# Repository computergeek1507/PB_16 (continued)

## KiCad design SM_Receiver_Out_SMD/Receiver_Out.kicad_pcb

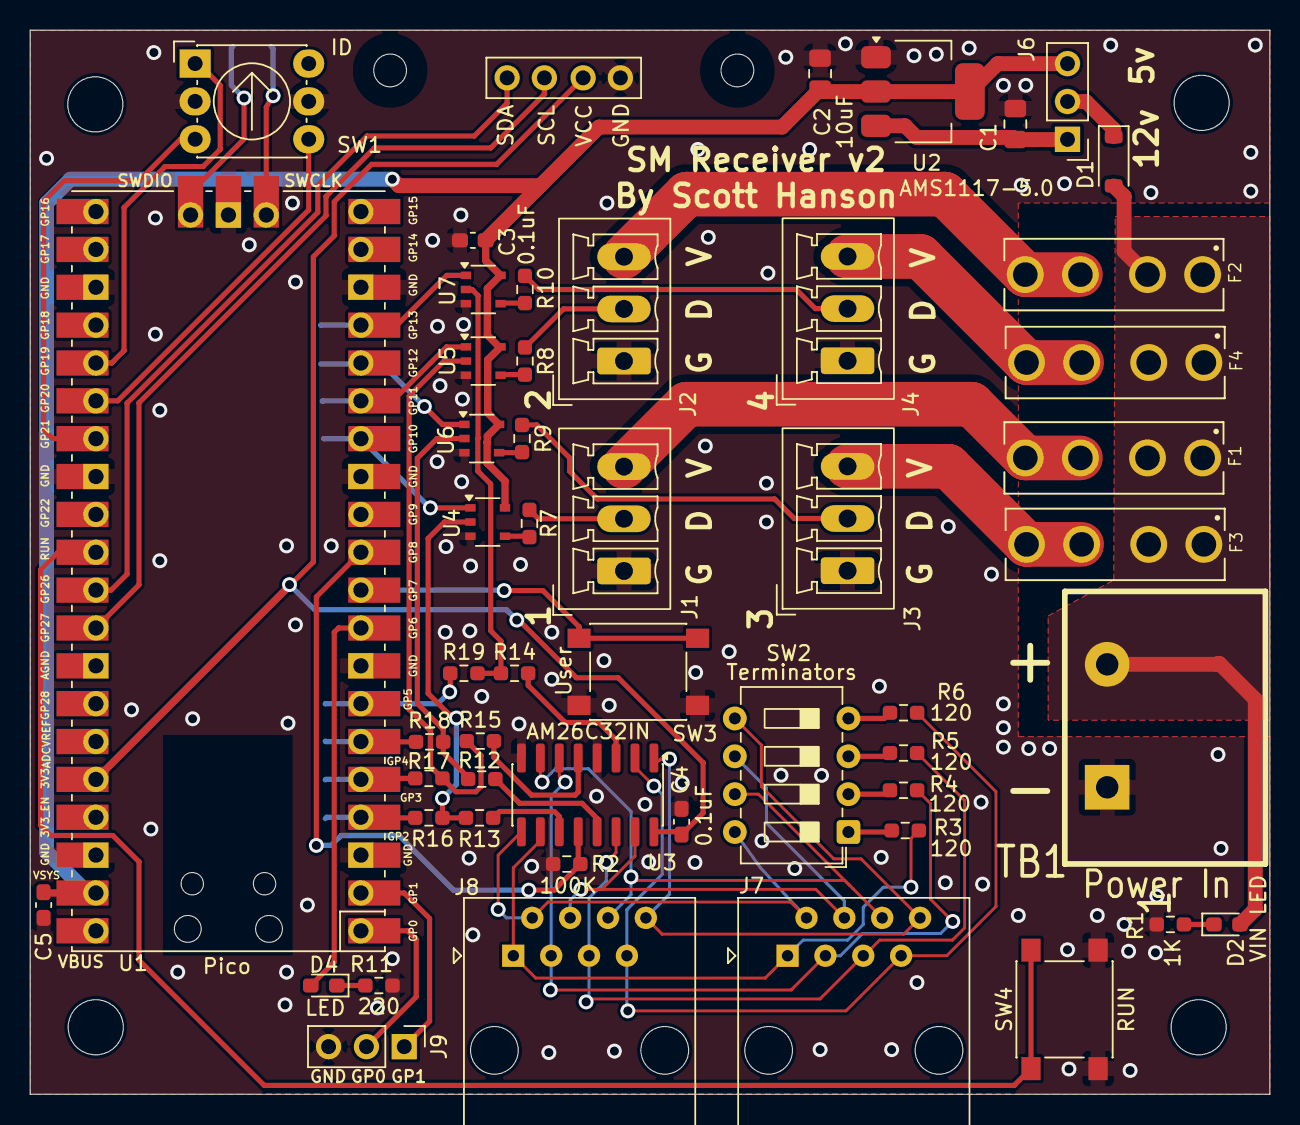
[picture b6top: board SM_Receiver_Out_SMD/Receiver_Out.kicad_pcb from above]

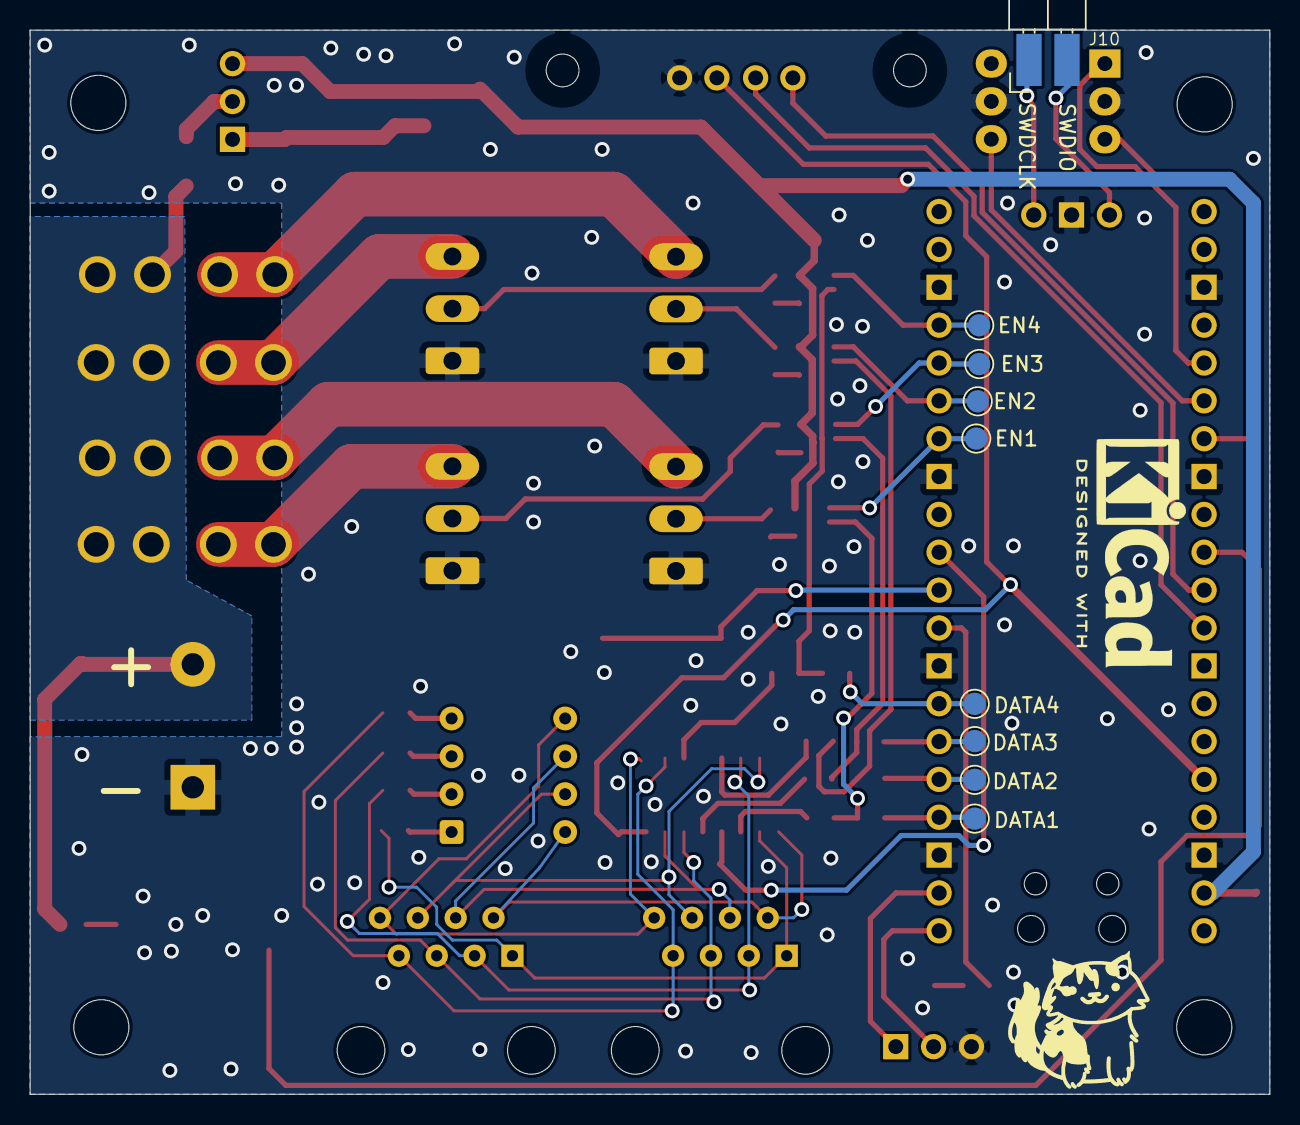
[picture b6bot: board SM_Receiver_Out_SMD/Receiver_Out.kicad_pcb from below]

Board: 2 copper layers, 83.2 x 71.4 mm, 65 parts (9 on the bottom side), 61 nets.

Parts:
C1, C2: 10uF; C_0805_2012Metric_Pad1.18x1.45mm_HandSolder
C3, C4, C5: 0.1uF; C_0603_1608Metric_Pad1.08x0.95mm_HandSolder
D1: B5819W; D_SOD-123
D2: VIN LED; LED_0603_1608Metric_Pad1.05x0.95mm_HandSolder
D4: LED; LED_0603_1608Metric_Pad1.05x0.95mm_HandSolder
F1, F2, F3, F4: 3544-2; FUSE_3544-2
H1, H2, H3, H4: MountingHole; MountingHole_3.7mm
J1: String1; PhoenixContact_MCV_1,5_3-G-3.5_1x03_P3.50mm_Vertical
J2: String2; PhoenixContact_MCV_1,5_3-G-3.5_1x03_P3.50mm_Vertical
J3: String3; PhoenixContact_MCV_1,5_3-G-3.5_1x03_P3.50mm_Vertical
J4: String4; PhoenixContact_MCV_1,5_3-G-3.5_1x03_P3.50mm_Vertical
J5: OLED; OLED-SSD1306-128X64-I2C-THT
J6: VIN_Voltage; PinHeader_1x03_P2.54mm_Vertical
J7, J8: RJ45; RJ45_Amphenol_54602-x08_Horizontal
J9: Debug; PinHeader_1x03_P2.54mm_Vertical
J10: SWD; 1x02_Horizontal_SMD
R1: 1K; R_0603_1608Metric_Pad0.98x0.95mm_HandSolder
R2: 100K; R_0603_1608Metric_Pad0.98x0.95mm_HandSolder
R3, R4, R5, R6: 120; R_0603_1608Metric_Pad0.98x0.95mm_HandSolder
R7, R8, R9, R10: 33ohm; R_0603_1608Metric_Pad0.98x0.95mm_HandSolder
R11: 220; R_0603_1608Metric_Pad0.98x0.95mm_HandSolder
R12, R13, R14, R15, R16, R17, R18, R19: 100ohm; R_0603_1608Metric_Pad0.98x0.95mm_HandSolder
SW1: ID; Nidec_Copal_SH-7010C
SW2: Terminators; SW_DIP_SPSTx04_Slide_6.7x11.72mm_W7.62mm_P2.54mm_LowProfile
SW3: User; SW_Push_1P1T_NO_6x6mm_H9.5mm
SW4: RUN; SW_Push_1P1T_NO_6x6mm_H9.5mm
TB1: Power In; BARRIER_BLOCK_1ROW_2POS
TP1: DATA1; TestPoint_Pad_D1.5mm
TP2: DATA2; TestPoint_Pad_D1.5mm
TP3: DATA3; TestPoint_Pad_D1.5mm
TP4: DATA4; TestPoint_Pad_D1.5mm
TP5: EN1; TestPoint_Pad_D1.5mm
TP6: EN2; TestPoint_Pad_D1.5mm
TP7: EN3; TestPoint_Pad_D1.5mm
TP8: EN4; TestPoint_Pad_D1.5mm
U1: Pico; RPi_Pico_SMD_TH
U2: AMS1117-5.0; SOT-223-3_TabPin2
U3: AM26C32IN; SOIC-16_3.9x9.9mm_P1.27mm
U4, U5, U6, U7: 74AHCT1G125; TSOP-5_1.65x3.05mm_P0.95mm

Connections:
+3V3: C4.1, J5.3, U1.36 (3V3), U3.16 (VCC)
+5V: C2.1, C3.1, C5.1, J6.3, U1.39 (VSYS), U2.2 (VO), U4.5 (VCC), U5.5 (VCC), U6.5 (VCC), U7.5 (VCC)
/Micro/SCL: J5.2, U1.32 (GPIO27_ADC1)
/Micro/SDA: J5.1, U1.31 (GPIO26_ADC0)
/Micro/SWDCLK: J10.1, U1.41 (SWCLK)
/Micro/SWDIO: J10.2, U1.43 (SWDIO)
/Outputs/DOUT1: J1.2, R7.1
/Outputs/DOUT2: J2.2, R8.1
/Outputs/DOUT3: J3.2, R9.1
/Outputs/DOUT4: J4.2, R10.1
/Outputs/VOUT1: F1.2_1 (2), F1.2_2 (2), J1.3
/Outputs/VOUT2: F2.2_1 (2), F2.2_2 (2), J2.3
/Outputs/VOUT3: F3.2_1 (2), F3.2_2 (2), J3.3
/Outputs/VOUT4: F4.2_1 (2), F4.2_2 (2), J4.3
/PWR: C1.1, J6.1, U2.3 (VI)
/VIN: D1.1 (K), J6.2
DIFF_EN: R2.1, U1.11 (GPIO8), U3.12 (EN_2)
EN1: TP5.1, U1.14 (GPIO10), U4.1
EN2: TP6.1, U1.15 (GPIO11), U5.1
EN3: TP7.1, U1.16 (GPIO12), U6.1
EN4: TP8.1, U1.17 (GPIO13), U7.1
GND: C1.2, C2.2, C3.2, C4.2, C5.2, J1.1, J2.1, J3.1, J4.1, J5.4, J9.3, R1.1, R2.2, R11.2, SW1.C, SW3.1, SW4.2, TB1.1, U1.3 (GND), U1.8 (GND), U1.13 (GND), U1.18 (GND), U1.23 (GND), U1.28 (GND), U1.38 (GND), U1.42 (GND), U2.1 (GND), U3.4 (EN), U3.8 (GND), U4.3 (GND), U5.3 (GND), U6.3 (GND), U7.3 (GND)
unnamed: D2.1 (K), R1.2
unnamed: D4.1 (K), R11.1
unnamed: D4.2 (A), U1.9 (GPIO6)
unnamed: J9.1, U1.2 (GPIO1)
unnamed: J9.2, U1.1 (GPIO0)
unnamed: R3.1, SW2.1
unnamed: R4.1, SW2.2
unnamed: R5.1, SW2.3
unnamed: R6.1, SW2.4
unnamed: R7.2, U4.4
unnamed: R8.2, U5.4
unnamed: R9.2, U6.4
unnamed: R10.2, U7.4
unnamed: R12.1, U3.13 (OUT_B)
unnamed: R13.1, U3.11 (OUT_D)
unnamed: R14.2, U3.3 (OUT_A)
unnamed: R15.2, U3.5 (OUT_C)
unnamed: R16.1, TP1.1, U1.4 (GPIO2)
unnamed: R17.1, TP2.1, U1.5 (GPIO3)
unnamed: R18.1, TP3.1, U1.6 (GPIO4)
unnamed: R19.1, TP4.1, U1.7 (GPIO5)
unnamed: SW1.1, U1.25 (GPIO19)
unnamed: SW1.2, U1.26 (GPIO20)
unnamed: SW1.4, U1.27 (GPIO21)
unnamed: SW3.2, U1.10 (GPIO7)
unnamed: SW4.1, U1.30 (RUN)
OUT17: R13.2, R16.2, U4.2
OUT18: R15.1, R17.2, U5.2
OUT19: R12.2, R18.2, U6.2
OUT20: R14.1, R19.2, U7.2
Serial1_N: J7.2, J8.2, SW2.8, U3.9 (INPUT_D-)
Serial1_P: J7.1, J8.1, R3.2, U3.10 (INPUT_D+)
Serial2_N: J7.6, J8.6, SW2.7, U3.7 (INPUT_C-)
Serial2_P: J7.3, J8.3, R4.2, U3.6 (INPUT_C+)
Serial3_N: J7.4, J8.4, SW2.6, U3.15 (INPUT_B-)
Serial3_P: J7.5, J8.5, R5.2, U3.14 (INPUT_B+)
Serial4_N: J7.8, J8.8, SW2.5, U3.1 (INPUT_A-)
Serial4_P: J7.7, J8.7, R6.2, U3.2 (INPUT_A+)
VIN1: D1.2 (A), D2.2 (A), F1.1_1 (1), F1.1_2 (1), F2.1_1 (1), F2.1_2 (1), F3.1_1 (1), F3.1_2 (1), F4.1_1 (1), F4.1_2 (1), TB1.2

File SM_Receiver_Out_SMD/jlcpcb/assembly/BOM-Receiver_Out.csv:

Comment,Designator,Footprint,LCSC
User,"SW3,SW4",SW_Push_1P1T_NO_6x6mm_H9.5mm,C127509
0.1uF,"C3,C4,C5",C_0603_1608Metric_Pad1.08x0.95mm_HandSolder,C1525
10uF,"C1,C2",C_0805_2012Metric_Pad1.18x1.45mm_HandSolder,C15850
String1,"J1,J2,J3,J4","PhoenixContact_MCV_1,5_3-G-3.5_1x03_P3.50mm_Vertical",C192778
1K,R1,R_0603_1608Metric_Pad0.98x0.95mm_HandSolder,C21190
OLED,J5,OLED-SSD1306-128X64-I2C-THT,C225501
100ohm,"R12,R13,R14,R15,R16,R17,R18,R19",R_0603_1608Metric_Pad0.98x0.95mm_HandSolder,C22775
120,"R3,R4,R5,R6",R_0603_1608Metric_Pad0.98x0.95mm_HandSolder,C22787
VIN LED,"D2,D4",LED_0603_1608Metric_Pad1.05x0.95mm_HandSolder,C2286
220,R11,R_0603_1608Metric_Pad0.98x0.95mm_HandSolder,C22962
33ohm,"R10,R7,R8,R9",R_0603_1608Metric_Pad0.98x0.95mm_HandSolder,C23140
100K,R2,R_0603_1608Metric_Pad0.98x0.95mm_HandSolder,C25803
RJ45,"J7,J8",RJ45_Amphenol_54602-x08_Horizontal,C2938579
Power In,TB1,BARRIER_BLOCK_1ROW_2POS,C306200
ID,SW1,Nidec_Copal_SH-7010C,C457921
SWD,J10,1x02_Horizontal_SMD,C492401
VIN_Voltage,"J6,J9",PinHeader_1x03_P2.54mm_Vertical,C49257
3544-2,"F1,F2,F3,F4",FUSE_3544-2,C492610
Terminators,SW2,SW_DIP_SPSTx04_Slide_6.7x11.72mm_W7.62mm_P2.54mm_LowProfile,C509571
AM26C32IN,U3,SOIC-16_3.9x9.9mm_P1.27mm,C6180
AMS1117-5.0,U2,SOT-223-3_TabPin2,C6187
74AHCT1G125,"U4,U5,U6,U7",TSOP-5_1.65x3.05mm_P0.95mm,C7484
B5819W,D1,D_SOD-123,C8598
Pico,U1,RPi_Pico_SMD_TH,

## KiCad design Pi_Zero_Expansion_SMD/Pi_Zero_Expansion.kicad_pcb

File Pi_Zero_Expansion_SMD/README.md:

# Copyright and Disclaimer
Copyright: Scott Hanson

This documentation describes Open Hardware and is licensed under the CERN Open Hardware Licence Version 2 - Strongly Reciprocal. (CERN-OHL-S)

You may redistribute and modify this documentation under the terms of the CERN OHL-S-v2 (https://ohwr.org/cern_ohl_s_v2.txt). This documentation is distributed WITHOUT ANY EXPRESS OR IMPLIED WARRANTY, INCLUDING OF MERCHANTABILITY, SATISFACTORY QUALITY AND FITNESS FOR A PARTICULAR PURPOSE. Please see the CERN OHL v2-S for applicable conditions

**Under CERN OHL-S-v2, derivative work must be publicy released as defined in subsection 3.3**

# Pi Zero Expansion 

The Pi Zero Expansion is a surface mount(SMD) controller with a single Expansion port. A total of 16 pixel outputs. All the design files are open source and available on github.

## [Interactive BOM](https://computergeek1507.github.io/PB_16/Pi_Zero_Expansion_SMD/bom/ibom)

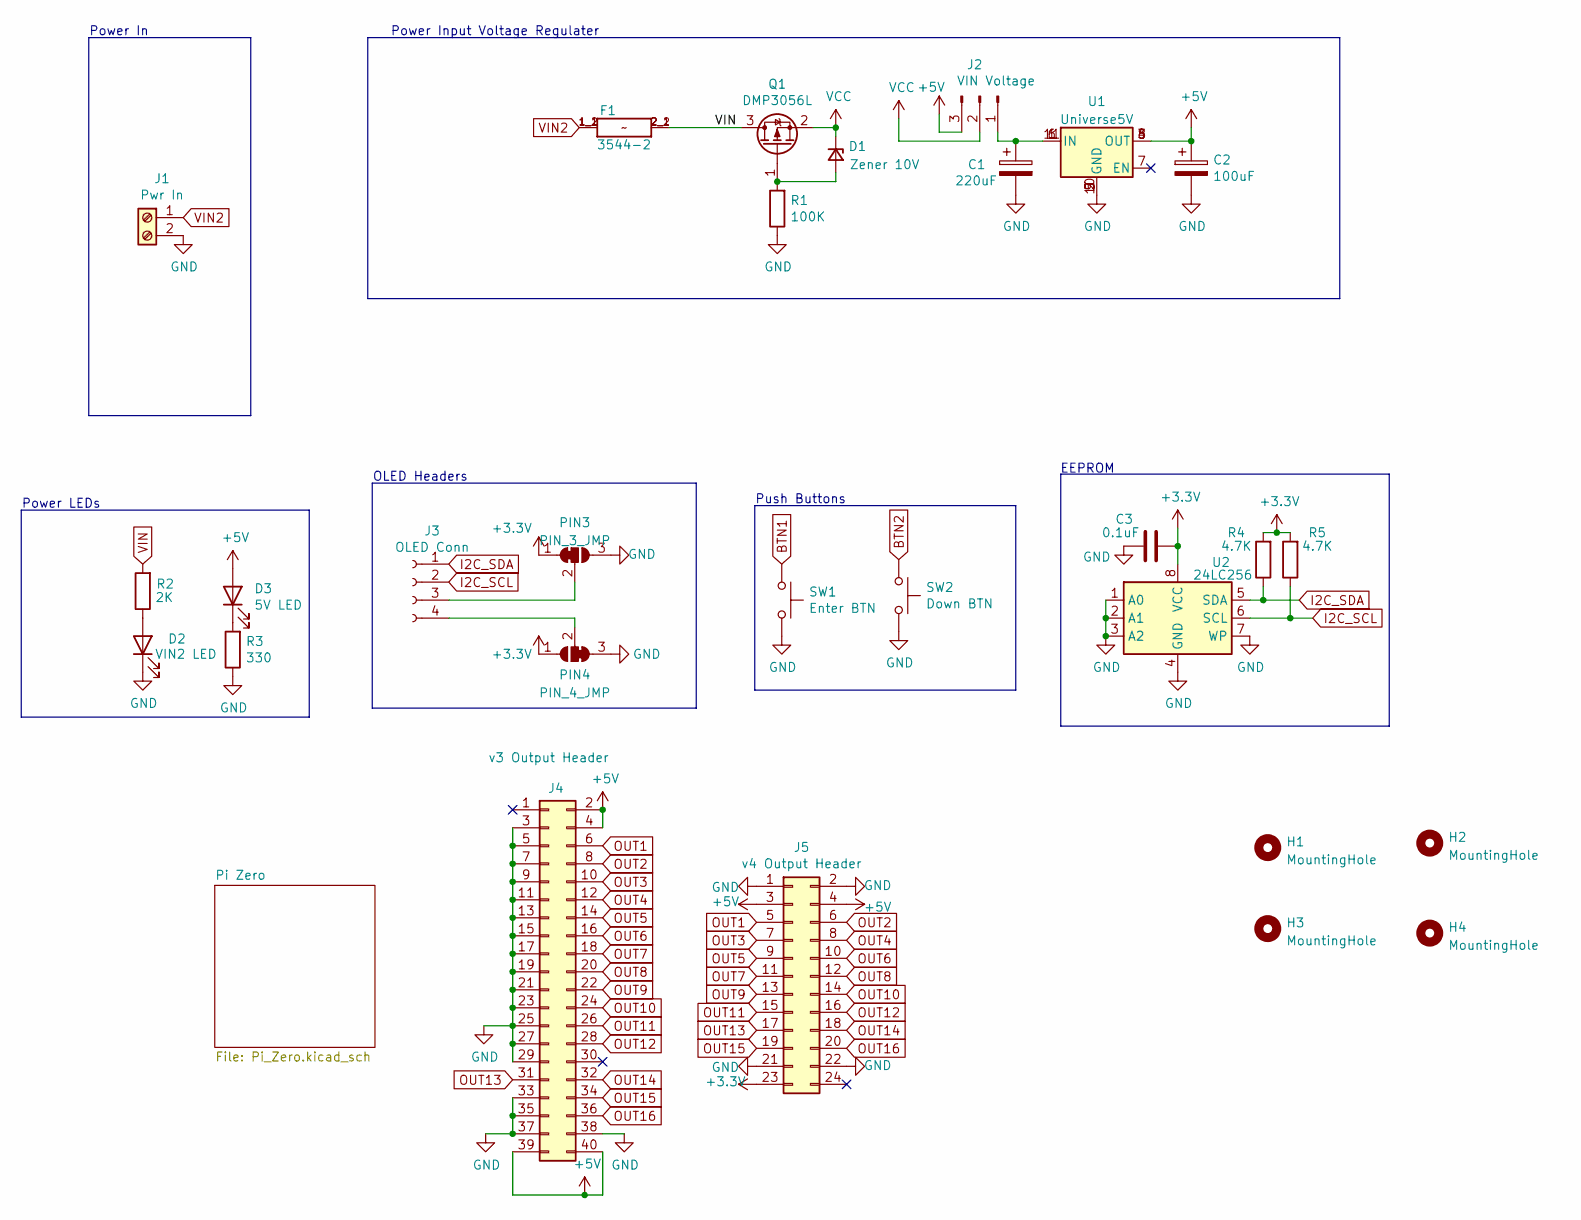
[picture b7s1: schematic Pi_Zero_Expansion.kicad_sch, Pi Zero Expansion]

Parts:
C1: 220uF; CP_Radial_D10.0mm_P5.00mm; MPN ECA-1HM221; Digi-Key_PN P5183-ND
C2: 100uF; CP_Elec_6.3x5.4_Nichicon; MPN UWX1C101MCL1GB; Digi-Key_PN 493-2105-1-ND
C3: 0.1uF; C_0603_1608Metric_Pad1.08x0.95mm_HandSolder; MPN CL10B104KB8NNWC; Digi-Key_PN 1276-1935-2-ND
D1: Zener 10V; D_SOD-123; MPN MMSZ5240B-7-F; Digi-Key_PN MMSZ5240B-FDICT-ND
D2: VIN2 LED; LED_0603_1608Metric_Pad1.05x0.95mm_HandSolder; MPN LTST-C190KRKT; Digi-Key_PN 160-1436-2-ND
D3: 5V LED; LED_0603_1608Metric_Pad1.05x0.95mm_HandSolder; MPN LTST-C190KRKT; Digi-Key_PN 160-1436-2-ND
F1: 3544-2; FUSE_3544-2; MPN 3544-2; Digi-Key_PN 36-3544-2-ND
H1, H2, H3, H4: MountingHole; MountingHole_3.7mm
J1: Pwr In; PHOENIX_MKDS1_2-3.81; MPN 1727010; Digi-Key_PN 277-1947-ND
J2: VIN Voltage; PinHeader_1x03_P2.54mm_Vertical; MPN 61300311121; Digi-Key_PN 732-5316-ND
J3: OLED Conn; PinSocket_1x04_P2.54mm_Vertical; MPN PPTC041LFBN-RC; Digi-Key_PN S7002-ND
J4: v3 Output Header; IDC-Header_2x20_P2.54mm_Vertical; MPN SBH11-PBPC-D20-ST-BK; Digi-Key_PN S9175-ND
J5: v4 Output Header; IDC-Header_2x12_P2.54mm_Vertical; MPN Z-S311024S1GK1A; Digi-Key_PN ED10525-ND
PIN3: PIN_3_JMP; SolderJumper-3_P1mm_Bridged12
PIN4: PIN_4_JMP; SolderJumper-3_P1mm_Bridged23
Q1: DMP3056L; SOT-23; MPN DMP3056L-7; Digi-Key_PN DMP3056L-7DICT-ND
R1: 100K; R_0603_1608Metric_Pad0.98x0.95mm_HandSolder; MPN RT0603BRD07100KL; Digi-Key_PN YAG1235CT-ND
R2: 2K; R_0603_1608Metric_Pad0.98x0.95mm_HandSolder; LCSC C4190
R3: 330; R_0603_1608Metric_Pad0.98x0.95mm_HandSolder; LCSC C23138
R4, R5: 4.7K; R_0603_1608Metric_Pad0.98x0.95mm_HandSolder; MPN RC0603JR-074K7L; Digi-Key_PN 311-4.7KGRCT-ND
SW1: Enter BTN; SW_Push_1P1T_NO_6x6mm_H9.5mm; MPN PTS645SL50SMTR92 LFS; Digi-Key_PN CKN9088CT-ND
SW2: Down BTN; SW_Push_1P1T_NO_6x6mm_H9.5mm; MPN PTS645SL50SMTR92 LFS; Digi-Key_PN CKN9088CT-ND
U1: Universe5V; Universal_5V_Horizontal
U2: 24LC256; SOIC-8_3.9x4.9mm_P1.27mm; MPN 24LC256T-I/SN; Digi-Key_PN 24LC256T-I/SNCT-ND

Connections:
+3V3: C3.1, J5.23, PIN3.1 (A), PIN4.1 (A), R4.2, R5.2, U2.8 (VCC); also elsewhere on the board
+5V: C2.1, D3.2 (A), J2.3, J4.2, J4.4, J4.39, J4.40, J5.3, J5.4, U1.3 (OUT), U1.4 (OUT), U1.8 (OUT); also elsewhere on the board
BTN1: SW1.1; also elsewhere on the board
BTN2: SW2.1; also elsewhere on the board
GND: C1.2, C2.2, C3.2, D2.1 (K), J1.2, J4.3, J4.5, J4.7, J4.9, J4.11, J4.13, J4.15, J4.17, J4.19, J4.21, J4.23, J4.25, J4.27, J4.29, J4.33, J4.35, J4.37, J4.38, J5.1, J5.2, J5.21, J5.22, PIN3.3 (B), PIN4.3 (B), R1.1, R3.1, SW1.2, SW2.2, U1.2 (GND), U1.5 (GND), U1.9 (GND), U1.10 (GND), U2.1 (A0), U2.2 (A1), U2.3 (A2), U2.4 (GND), U2.7 (WP); also elsewhere on the board
I2C_SCL: J3.2, R5.1, U2.6 (SCL); also elsewhere on the board
I2C_SDA: J3.1, R4.1, U2.5 (SDA); also elsewhere on the board
unnamed: C1.1, J2.1, U1.1 (IN), U1.6 (IN), U1.11 (IN)
unnamed: D1.2 (A), Q1.1 (G), R1.2
unnamed: D2.2 (A), R2.1
unnamed: D3.1 (K), R3.2
unnamed: J3.3, PIN3.2 (C)
unnamed: J3.4, PIN4.2 (C)
OUT1: J4.6, J5.5; also elsewhere on the board
OUT2: J4.8, J5.6; also elsewhere on the board
OUT3: J4.10, J5.7; also elsewhere on the board
OUT4: J4.12, J5.8; also elsewhere on the board
OUT5: J4.14, J5.9; also elsewhere on the board
OUT6: J4.16, J5.10; also elsewhere on the board
OUT7: J4.18, J5.11; also elsewhere on the board
OUT8: J4.20, J5.12; also elsewhere on the board
OUT9: J4.22, J5.13; also elsewhere on the board
OUT10: J4.24, J5.14; also elsewhere on the board
OUT11: J4.26, J5.15; also elsewhere on the board
OUT12: J4.28, J5.16; also elsewhere on the board
OUT13: J4.31, J5.17; also elsewhere on the board
OUT14: J4.32, J5.18; also elsewhere on the board
OUT15: J4.34, J5.19; also elsewhere on the board
OUT16: J4.36, J5.20; also elsewhere on the board
VCC: D1.1 (K), J2.2, Q1.2 (S)
VIN: F1.2_1 (2), F1.2_2 (2), Q1.3 (D), R2.2
VIN2: F1.1_1 (1), F1.1_2 (1), J1.1

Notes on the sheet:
Power LEDs
Power In
OLED Headers
Push Buttons
Power Input Voltage Regulater
EEPROM

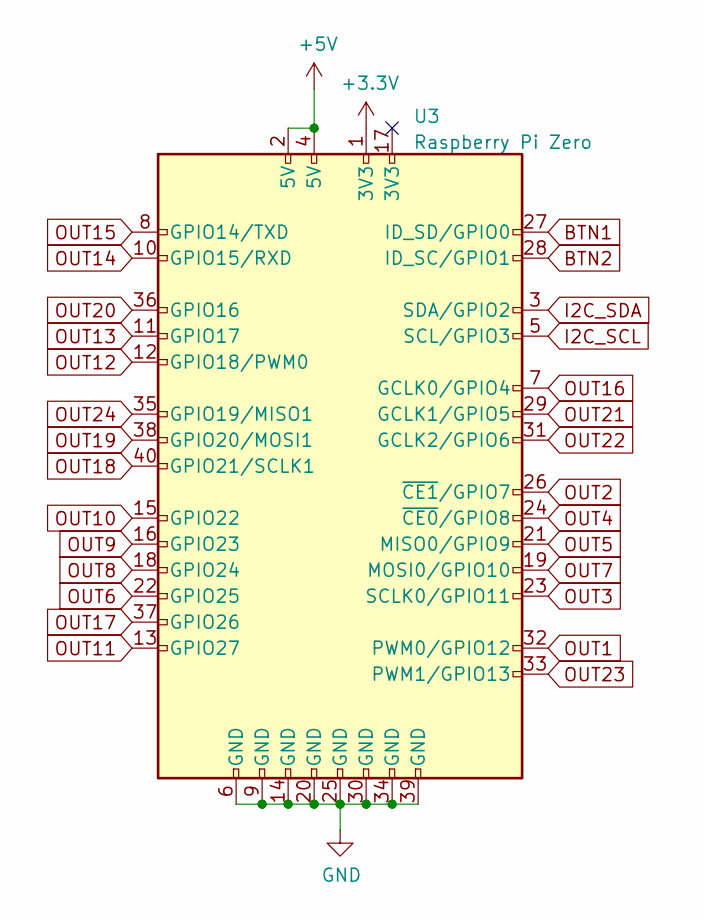
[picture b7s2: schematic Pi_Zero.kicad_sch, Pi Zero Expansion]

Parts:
U3: Raspberry Pi Zero; Raspberry_Pi_Zero_Socketed_THT_FaceDown_MountingHoles

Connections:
+3V3: U3.1 (3V3); also elsewhere on the board
+5V: U3.2 (5V), U3.4 (5V); also elsewhere on the board
BTN1: U3.27 (ID_SD/GPIO0); also elsewhere on the board
BTN2: U3.28 (ID_SC/GPIO1); also elsewhere on the board
GND: U3.6 (GND), U3.9 (GND), U3.14 (GND), U3.20 (GND), U3.25 (GND), U3.30 (GND), U3.34 (GND), U3.39 (GND); also elsewhere on the board
I2C_SCL: U3.5 (SCL/GPIO3); also elsewhere on the board
I2C_SDA: U3.3 (SDA/GPIO2); also elsewhere on the board
OUT1: U3.32 (PWM0/GPIO12); also elsewhere on the board
OUT2: U3.26 (~CE1/GPIO7); also elsewhere on the board
OUT3: U3.23 (SCLK0/GPIO11); also elsewhere on the board
OUT4: U3.24 (~CE0/GPIO8); also elsewhere on the board
OUT5: U3.21 (MISO0/GPIO9); also elsewhere on the board
OUT6: U3.22 (GPIO25); also elsewhere on the board
OUT7: U3.19 (MOSI0/GPIO10); also elsewhere on the board
OUT8: U3.18 (GPIO24); also elsewhere on the board
OUT9: U3.16 (GPIO23); also elsewhere on the board
OUT10: U3.15 (GPIO22); also elsewhere on the board
OUT11: U3.13 (GPIO27); also elsewhere on the board
OUT12: U3.12 (GPIO18/PWM0); also elsewhere on the board
OUT13: U3.11 (GPIO17); also elsewhere on the board
OUT14: U3.10 (GPIO15/RXD); also elsewhere on the board
OUT15: U3.8 (GPIO14/TXD); also elsewhere on the board
OUT16: U3.7 (GCLK0/GPIO4); also elsewhere on the board
OUT17: U3.37 (GPIO26)
OUT18: U3.40 (GPIO21/SCLK1)
OUT19: U3.38 (GPIO20/MOSI1)
OUT20: U3.36 (GPIO16)
OUT21: U3.29 (GCLK1/GPIO5)
OUT22: U3.31 (GCLK2/GPIO6)
OUT23: U3.33 (PWM1/GPIO13)
OUT24: U3.35 (GPIO19/MISO1)

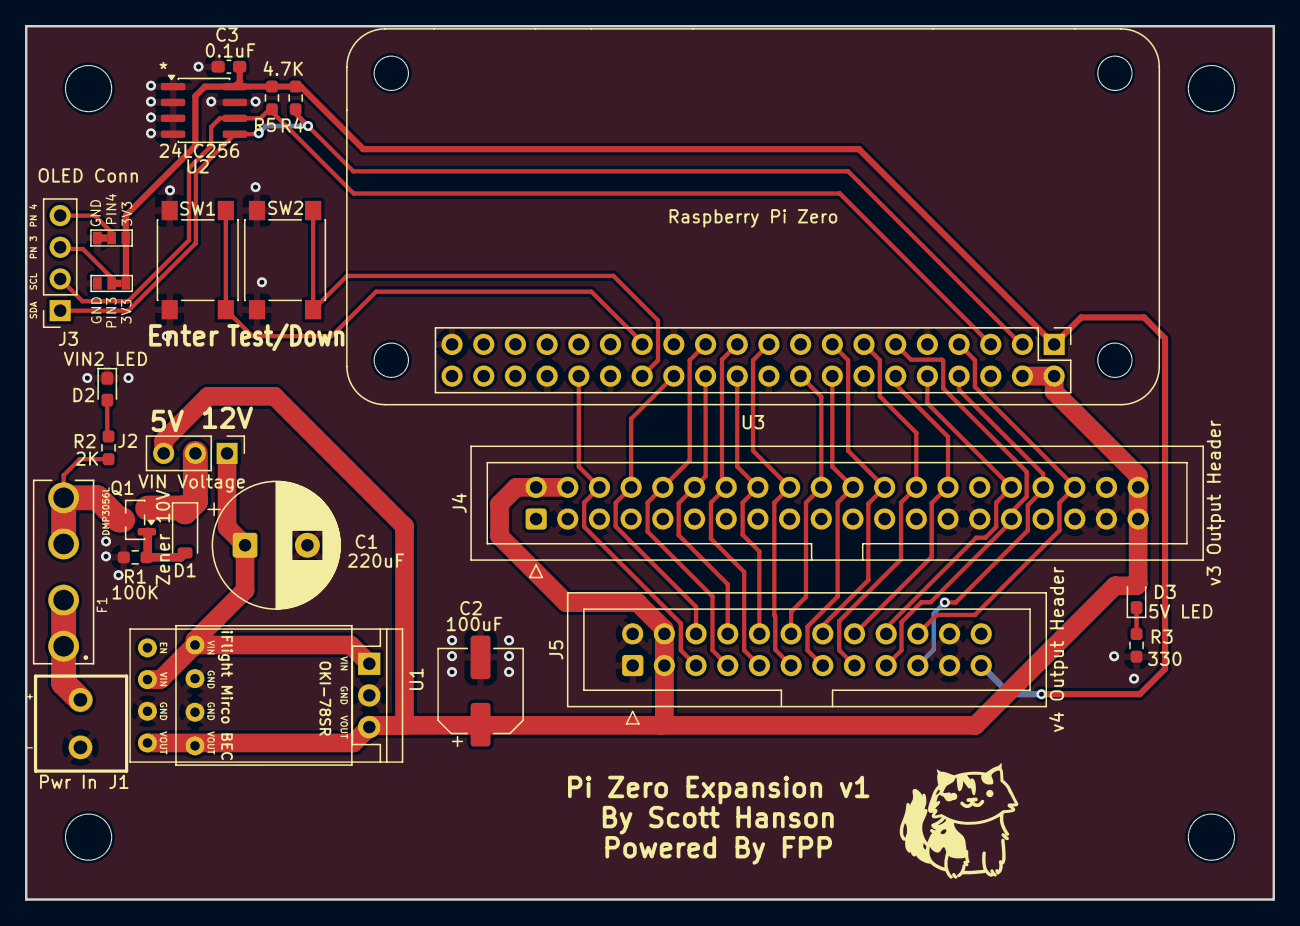
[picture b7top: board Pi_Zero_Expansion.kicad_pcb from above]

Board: 2 copper layers, 100.0 x 70.0 mm, 29 parts (1 on the bottom side), 32 nets.

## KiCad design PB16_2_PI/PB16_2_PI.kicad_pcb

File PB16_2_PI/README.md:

# Copyright and Disclaimer
Copyright: Scott Hanson

This documentation describes Open Hardware and is licensed under the CERN OHL v. 1.2.

You may redistribute and modify this documentation under the terms of the CERN OHL v.1.2. (http://ohwr.org/cernohl). This documentation is distributed WITHOUT ANY EXPRESS OR IMPLIED WARRANTY, INCLUDING OF MERCHANTABILITY, SATISFACTORY QUALITY AND FITNESS FOR A PARTICULAR PURPOSE. Please see the CERN OHL v.1.2 for applicable conditions

# PB16-2-PI

This is an adapter to use a Raspberry Pi W with the PB16 Cape instead of a PocketBeagle. This only supports the 16 local ports and the serial ports. The Expansion header does not work. Open source applications were used to create this PCB. [KiCad](http://kicad.org/) was used for the PCB design, and [LibreOffice](https://www.libreoffice.org/) for the documentation.

To order your own PCB upload the gerber.zip file to your favorite PCB manufacture of choice, I personally use [jlcpcb.com](https://jlcpcb.com/).

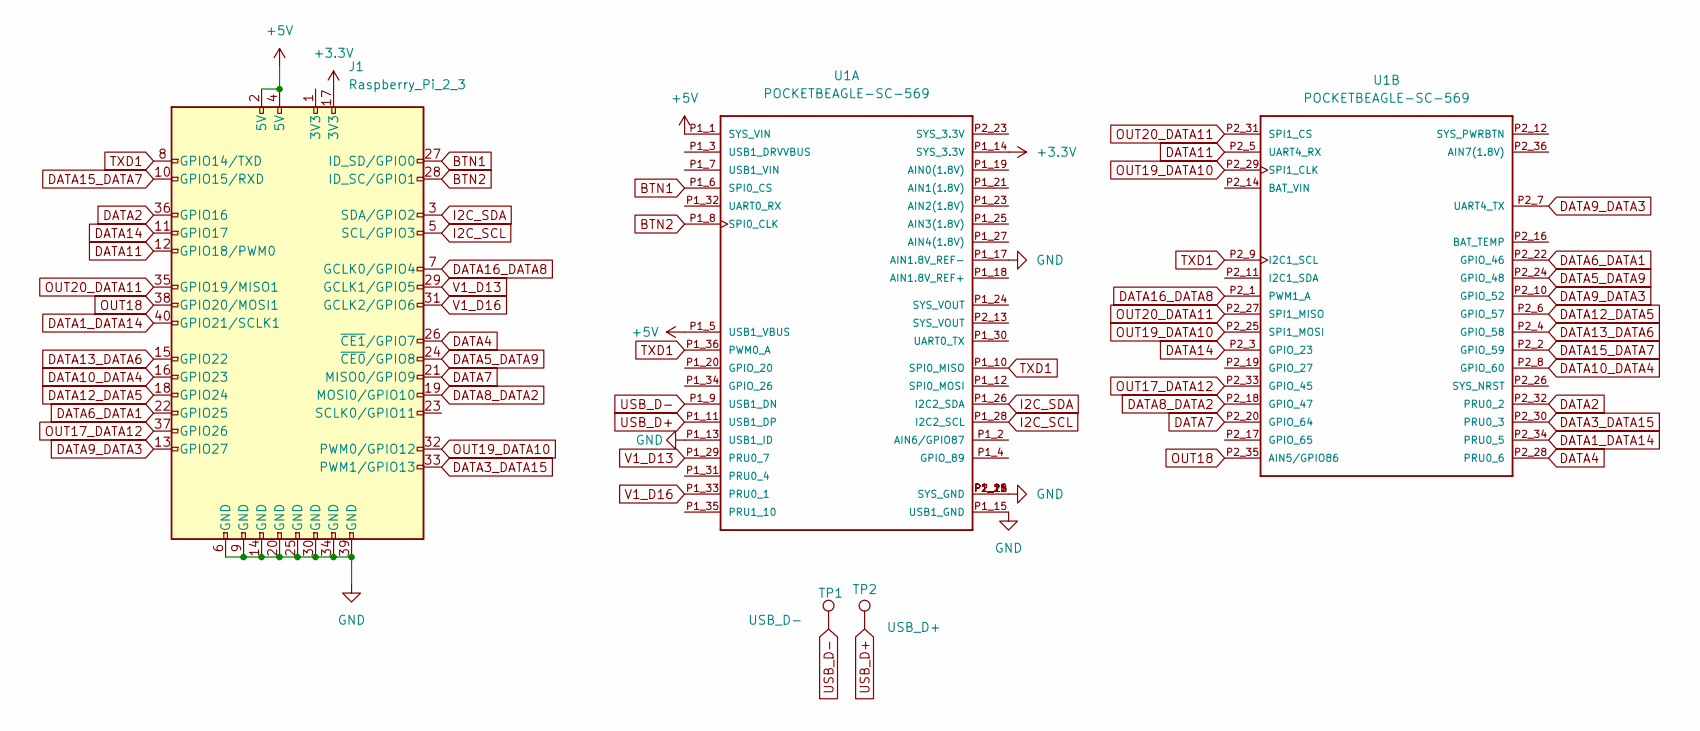
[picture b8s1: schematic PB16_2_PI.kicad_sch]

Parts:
J1: Raspberry_Pi_2_3; Raspberry_Pi_Zero_Socketed_THT_FaceDown_MountingHoles
TP1: USB_D-; TestPoint_THTPad_1.0x1.0mm_Drill0.5mm
TP2: USB_D+; TestPoint_THTPad_1.0x1.0mm_Drill0.5mm
U1: POCKETBEAGLE-SC-569; BEAGLE_POCKETBEAGLE-SC-569

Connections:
+3V3: J1.17 (3V3), U1.P1_14 (SYS_3.3V)
+5V: J1.2 (5V), J1.4 (5V), U1.P1_1 (SYS_VIN), U1.P1_5 (USB1_VBUS)
BTN1: J1.27 (ID_SD/GPIO0), U1.P1_6 (SPI0_CS)
BTN2: J1.28 (ID_SC/GPIO1), U1.P1_8 (SPI0_CLK)
DATA1_DATA14: J1.40 (GPIO21/SCLK1), U1.P2_34 (PRU0_5)
DATA2: J1.36 (GPIO16), U1.P2_32 (PRU0_2)
DATA3_DATA15: J1.33 (PWM1/GPIO13), U1.P2_30 (PRU0_3)
DATA4: J1.26 (~CE1/GPIO7), U1.P2_28 (PRU0_6)
DATA5_DATA9: J1.24 (~CE0/GPIO8), U1.P2_24 (GPIO_48)
DATA6_DATA1: J1.22 (GPIO25), U1.P2_22 (GPIO_46)
DATA7: J1.21 (MISO0/GPIO9), U1.P2_20 (GPIO_64)
DATA8_DATA2: J1.19 (MOSI0/GPIO10), U1.P2_18 (GPIO_47)
DATA9_DATA3: J1.13 (GPIO27), U1.P2_7 (UART4_TX), U1.P2_10 (GPIO_52)
DATA10_DATA4: J1.16 (GPIO23), U1.P2_8 (GPIO_60)
DATA11: J1.12 (GPIO18/PWM0), U1.P2_5 (UART4_RX)
DATA12_DATA5: J1.18 (GPIO24), U1.P2_6 (GPIO_57)
DATA13_DATA6: J1.15 (GPIO22), U1.P2_4 (GPIO_58)
DATA14: J1.11 (GPIO17), U1.P2_3 (GPIO_23)
DATA15_DATA7: J1.10 (GPIO15/RXD), U1.P2_2 (GPIO_59)
DATA16_DATA8: J1.7 (GCLK0/GPIO4), U1.P2_1 (PWM1_A)
GND: J1.6 (GND), J1.9 (GND), J1.14 (GND), J1.20 (GND), J1.25 (GND), J1.30 (GND), J1.34 (GND), J1.39 (GND), U1.P1_13 (USB1_ID), U1.P1_15 (USB1_GND), U1.P1_16 (SYS_GND), U1.P1_17 (AIN1.8V_REF-), U1.P1_22 (SYS_GND), U1.P2_15 (SYS_GND), U1.P2_21 (SYS_GND)
I2C_SCL: J1.5 (SCL/GPIO3), U1.P1_28 (I2C2_SCL)
I2C_SDA: J1.3 (SDA/GPIO2), U1.P1_26 (I2C2_SDA)
OUT17_DATA12: J1.37 (GPIO26), U1.P2_33 (GPIO_45)
OUT18: J1.38 (GPIO20/MOSI1), U1.P2_35 (AIN5/GPIO86)
OUT19_DATA10: J1.32 (PWM0/GPIO12), U1.P2_25 (SPI1_MOSI), U1.P2_29 (SPI1_CLK)
OUT20_DATA11: J1.35 (GPIO19/MISO1), U1.P2_27 (SPI1_MISO), U1.P2_31 (SPI1_CS)
TXD1: J1.8 (GPIO14/TXD), U1.P1_10 (SPI0_MISO), U1.P1_36 (PWM0_A), U1.P2_9 (I2C1_SCL)
USB_D+: TP2.1, U1.P1_11 (USB1_DP)
USB_D-: TP1.1, U1.P1_9 (USB1_DN)
V1_D13: J1.29 (GCLK1/GPIO5), U1.P1_29 (PRU0_7)
V1_D16: J1.31 (GCLK2/GPIO6), U1.P1_33 (PRU0_1)

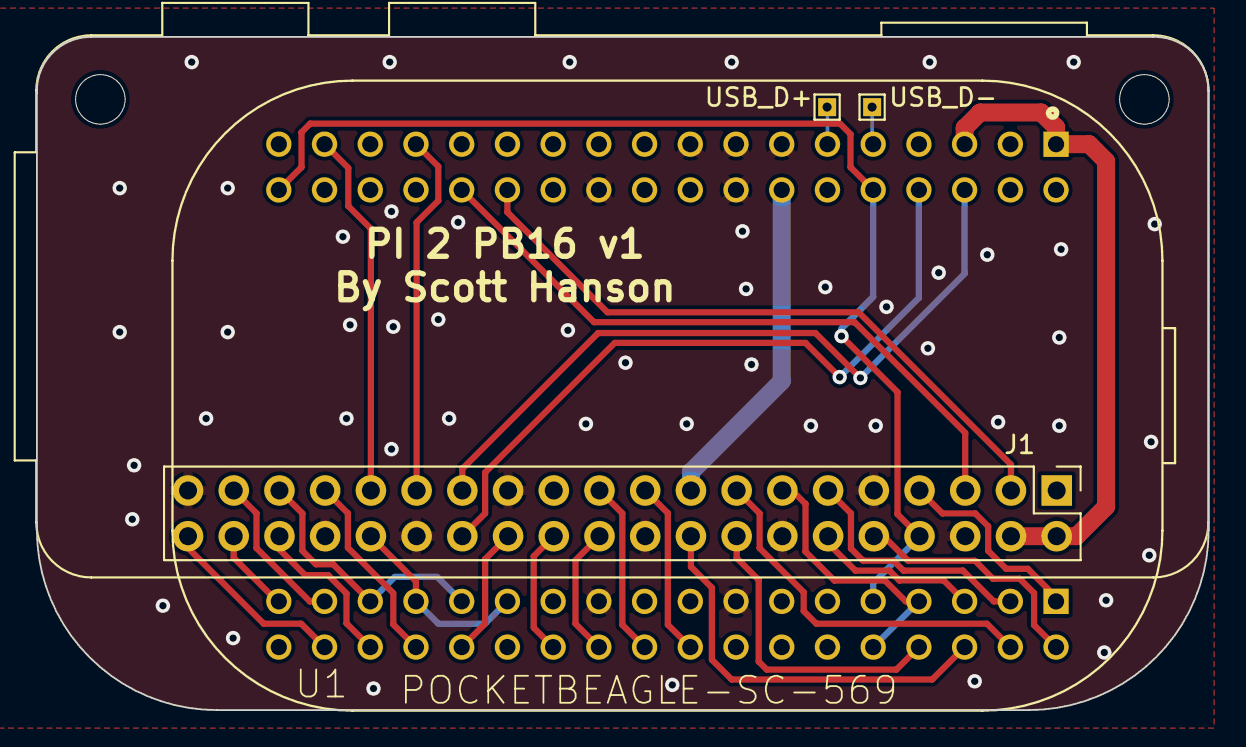
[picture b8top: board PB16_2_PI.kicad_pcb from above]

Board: 2 copper layers, 65.1 x 37.4 mm, 4 parts (1 on the bottom side), 32 nets.

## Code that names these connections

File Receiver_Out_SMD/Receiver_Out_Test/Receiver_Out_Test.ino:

#include <FAB_LED.h>
#include <OneButton.h>

const uint16_t numPixels = 300;

ws2812b<B,3> myLeds1;
ws2812b<B,0> myLeds2;
ws2812b<B,1> myLeds3;
ws2812b<B,2> myLeds4;
//ws2812b8s<B,0,7> strip_split8;//maybe?

volatile bool test_en = false;

volatile int mode = 0;

volatile unsigned long previousMillis = 0;

// constants won't change:
const long interval = 1000;

// --- WS2812 data detection on PB3, status LED on PA7 ---
const uint8_t DATA_PIN_BM = (1 << 3);    // PB3 bitmask within PORTB
const unsigned long dataTimeoutMs = 250; // consider data "lost" after this idle time
#define WS_DETECT_ISC PORT_ISC_RISING_gc // interrupt on rising edges (line idles low)
volatile bool wsActivity = false;        // set by the pin-change ISR on each edge
unsigned long lastDataMillis = 0;        // last time activity was seen on PB3
bool dataLedOn = false;                  // current state of the PA7 status LED

////////////////////////////////////////////////////////////////////////////////
/// @brief Pin-change ISR for PORTB.
/// The WS2812 line idles low and produces a rising edge for every bit clocked
/// in, so any edge means data is present. We only flag activity here; the loop
/// timestamps it. The PB3 interrupt is disabled while test mode drives PORTB.
////////////////////////////////////////////////////////////////////////////////
ISR(PORTB_PORT_vect)
{
  if (PORTB.INTFLAGS & DATA_PIN_BM)
  {
    PORTB.INTFLAGS = DATA_PIN_BM; // clear the flag (write 1 to clear)
    wsActivity = true;
  }
}

OneButton  button = OneButton (
  PIN_PA2,  // Input pin for the button
  true,        // Button is active LOW
  true         // Enable internal pull-up resistor
);

////////////////////////////////////////////////////////////////////////////////
/// @brief Display numPixels with one solid color.
/// We only use a 3 byte array, storing one pixel.
/// We then send the same pixel repeatedly to the LED strip very fast.
/// This demonstrates the ability tocall the library repeatedly.
/// If this feature fails, you may see only 1 pixel lit, or a varying number
/// of pixels glitching on and off.
////////////////////////////////////////////////////////////////////////////////
void color1N(uint8_t red, uint8_t green, uint8_t blue)
{
  rgb pix[1];

  pix[0].r = red;
  pix[0].g = green;
  pix[0].b = blue;

  // Disable interupts, save the old interupt state
  const uint8_t oldSREG = SREG;
  cli();

  // Display the LEDs. Each strip must be streamed contiguously: the gap
  // between successive sendPixels() calls on the SAME pin is only a few us,
  // well under the WS2812 latch time. Interleaving the four strips would
  // leave each line idle ~90us between its pixels, latching the strip after
  // the first pixel (symptom: only the first LED lights up).
  for (uint16_t i = 0; i < numPixels; i++) { myLeds1.sendPixels(1, pix); }
  for (uint16_t i = 0; i < numPixels; i++) { myLeds2.sendPixels(1, pix); }
  for (uint16_t i = 0; i < numPixels; i++) { myLeds3.sendPixels(1, pix); }
  for (uint16_t i = 0; i < numPixels; i++) { myLeds4.sendPixels(1, pix); }

  // Restore the old interrupt state
  SREG = oldSREG;
}

void LongPress(void * /*oneButton*/)
{
  if(test_en)
  {
    myLeds1.clear(numPixels);
    myLeds2.clear(numPixels);
    myLeds3.clear(numPixels);
    myLeds4.clear(numPixels);
    digitalWrite(PIN_PA1, LOW);
    //FAB_PORT(B, 0x00); // all pins low
    PORTB.DIR =    0b00000000;
    PORTB.PIN0CTRL = 0;
    PORTB.PIN1CTRL = 0;
    PORTB.PIN2CTRL = 0;
    PORTB.PIN3CTRL = WS_DETECT_ISC; // re-enable WS2812 data-detect interrupt on PB3
    digitalWrite(PIN_PC1, LOW);
  }
  else
  {
    digitalWrite(PIN_PC1, HIGH);
    digitalWrite(PIN_PA1, HIGH);
    FAB_PORT(B, 0x00); // all pins low
    FAB_DDR(B, 0xFF); // all pins out
    PORTB.PIN3CTRL = 0; // disable PB3 interrupt while test mode drives PORTB
    myLeds1.clear(numPixels);
    myLeds2.clear(numPixels);
    myLeds3.clear(numPixels);
    myLeds4.clear(numPixels);
    previousMillis = 0;
  }
  test_en = !test_en;
}

////////////////////////////////////////////////////////////////////////////////
/// @brief This method is automatically called once when the board boots.
////////////////////////////////////////////////////////////////////////////////
void setup()
{
  pinMode(PIN_PC1, OUTPUT);
  pinMode(PIN_PA1, OUTPUT);
  pinMode(PIN_PA7, OUTPUT);     // WS2812 data-present status LED
  digitalWrite(PIN_PA7, LOW);
  //digitalWrite(PIN_PC1, HIGH);

  // button.attachPress(ShortPress, &button);
  button.attachLongPressStart(LongPress, &button);
  button.setDebounceMs(20);
  button.setLongPressIntervalMs(1000);

  //FAB_PORT(B, 0x00); // all pins low
  PORTB.DIR = 0b00000000;
  PORTB.PIN0CTRL = 0;
  PORTB.PIN1CTRL = 0;
  PORTB.PIN2CTRL = 0;
  PORTB.PIN3CTRL = WS_DETECT_ISC; // enable WS2812 data-detect interrupt on PB3
  digitalWrite(PIN_PC1, LOW);
  digitalWrite(PIN_PA1, LOW);
}

void loop()
{
  button.tick();
  unsigned long currentMillis = millis();
  if (currentMillis - previousMillis >= interval)
  {
    previousMillis = currentMillis;
    if(test_en)
    {
      switch(mode) {
        case 0:
          color1N(127,0,0);
          mode = 1;
          break;
        case 1:
          color1N(0,127,0);
          mode = 2;
          break;
        case 2:
          color1N(0,0,127);
          mode = 0;
          break;
      }
    }
  }

  // WS2812 data detection (PB3) -> status LED (PA7).
  // Only valid while test mode is off, since test mode drives PORTB as outputs.
  if (!test_en)
  {
    // Atomically read & clear the activity flag set by the pin-change ISR.
    uint8_t oldSREG = SREG;
    cli();
    bool act = wsActivity;
    wsActivity = false;
    SREG = oldSREG;

    if (act)
    {
      lastDataMillis = currentMillis;
    }
    bool present = (currentMillis - lastDataMillis) < dataTimeoutMs;
    if (present != dataLedOn)
    {
      dataLedOn = present;
      digitalWrite(PIN_PA7, present ? HIGH : LOW);
    }
  }
  else if (dataLedOn)
  {
    // Entered test mode: turn the data-present LED off.
    dataLedOn = false;
    digitalWrite(PIN_PA7, LOW);
  }

  delay(10);
}
